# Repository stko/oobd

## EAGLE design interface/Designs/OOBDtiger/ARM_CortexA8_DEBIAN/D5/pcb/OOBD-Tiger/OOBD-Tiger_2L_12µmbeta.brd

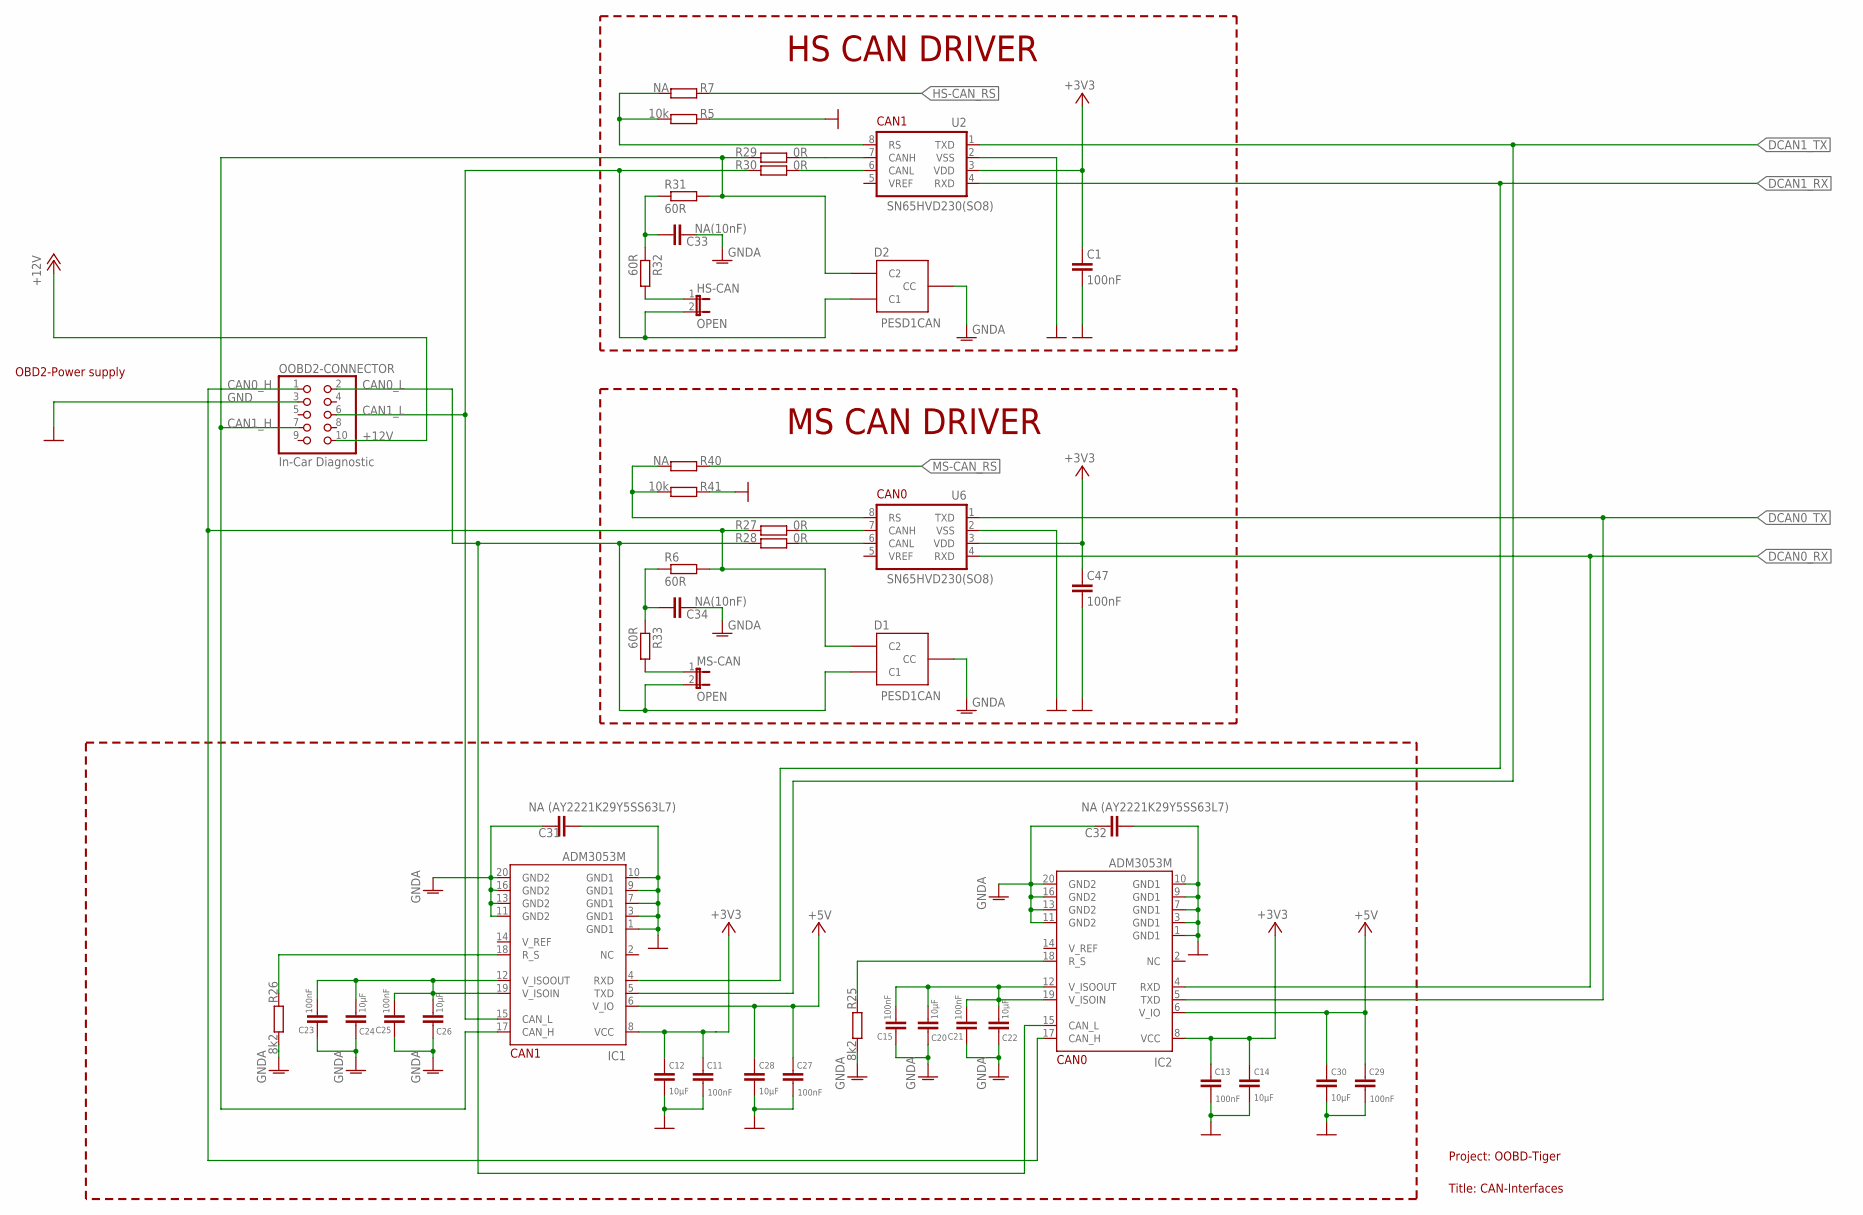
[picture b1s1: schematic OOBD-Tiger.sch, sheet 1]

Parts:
C1, C11, C13, C15, C21, C23, C25, C27, C29, C47: 100nF; C0603K
C12, C14, C20, C22, C24, C26, C28, C30: 10µF; C0805K
C31, C32: NA (AY2221K29Y5SS63L7); C075-032X103
C33, C34: NA(10nF); C0603
D1, D2: PESD1CAN; SOT23
HS-CAN: OPEN; 1X02
IC1, IC2: ADM3053M; SO20W
MS-CAN: OPEN; 1X02
OOBD2-CONNECTOR: In-Car Diagnostic; 2X05/90
R5, R41: 10k; R0603
R6, R31, R32, R33: 60R; R0603
R7, R40: NA; R0603
R25, R26: 8k2; R0603
R27, R28, R29, R30: 0R; 0207/10
U2, U6: SN65HVD230(SO8); SO-08

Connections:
+3V3: C1.1, C11.1, C12.1, C13.1, C14.1, C47.1, IC1.8 (VCC), IC2.8 (VCC), U2.3 (VDD), U6.3 (VDD); also elsewhere on the board
+5V: C27.1, C28.1, C29.1, C30.1, IC1.6 (V_IO), IC2.6 (V_IO); also elsewhere on the board
+12V: OOBD2-CONNECTOR.10; also elsewhere on the board
CAN0_H: D1.2 (C2), IC2.17 (CAN_H), OOBD2-CONNECTOR.1, R6.2, R27.1
CAN0_L: D1.1 (C1), IC2.15 (CAN_L), MS-CAN.2, OOBD2-CONNECTOR.2, R28.1
CAN1_H: D2.2 (C2), IC1.17 (CAN_H), OOBD2-CONNECTOR.7, R29.2, R31.2
CAN1_L: D2.1 (C1), HS-CAN.2, IC1.15 (CAN_L), OOBD2-CONNECTOR.6, R30.1
DCAN0_RX: IC2.4 (RXD), U6.4 (RXD); also elsewhere on the board
DCAN0_TX: IC2.5 (TXD), U6.1 (TXD); also elsewhere on the board
DCAN1_RX: IC1.4 (RXD), U2.4 (RXD); also elsewhere on the board
DCAN1_TX: IC1.5 (TXD), U2.1 (TXD); also elsewhere on the board
GND: C1.2, C11.2, C12.2, C13.2, C14.2, C27.2, C28.2, C29.2, C30.2, C31.2, C32.2, C47.2, IC1.1 (GND1), IC1.3 (GND1), IC1.7 (GND1), IC1.9 (GND1), IC1.10 (GND1), IC2.1 (GND1), IC2.3 (GND1), IC2.7 (GND1), IC2.9 (GND1), IC2.10 (GND1), OOBD2-CONNECTOR.3, R5.2, R41.2, U2.2 (VSS), U6.2 (VSS); also elsewhere on the board
GNDA: C15.2, C20.2, C21.2, C22.2, C23.2, C24.2, C25.2, C26.2, C31.1, C32.1, C33.2, C34.2, D1.3 (CC), D2.3 (CC), IC1.11 (GND2), IC1.13 (GND2), IC1.16 (GND2), IC1.20 (GND2), IC2.11 (GND2), IC2.13 (GND2), IC2.16 (GND2), IC2.20 (GND2), R25.1, R26.1
HS-CAN_RS: R7.2; also elsewhere on the board
MS-CAN_RS: R40.2; also elsewhere on the board
unnamed: C33.1, R31.1, R32.1
unnamed: R5.1, R7.1, U2.8 (RS)
unnamed: C34.1, R6.1, R33.1
unnamed: HS-CAN.1, R32.2
unnamed: C23.1, C24.1, C25.1, C26.1, IC1.12 (V_ISOOUT), IC1.19 (V_ISOIN)
unnamed: MS-CAN.1, R33.2
unnamed: IC2.18 (R_S), R25.2
unnamed: R27.2, U6.7 (CANH)
unnamed: R30.2, U2.6 (CANL)
unnamed: R28.2, U6.6 (CANL)
unnamed: R29.1, U2.7 (CANH)
unnamed: C15.1, C20.1, C21.1, C22.1, IC2.12 (V_ISOOUT), IC2.19 (V_ISOIN)
unnamed: IC1.18 (R_S), R26.2
unnamed: R40.1, R41.1, U6.8 (RS)

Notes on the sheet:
MS CAN DRIVER
HS CAN DRIVER
Project: OOBD-Tiger
Title: CAN-Interfaces
OBD2-Power supply
CAN1
CAN0

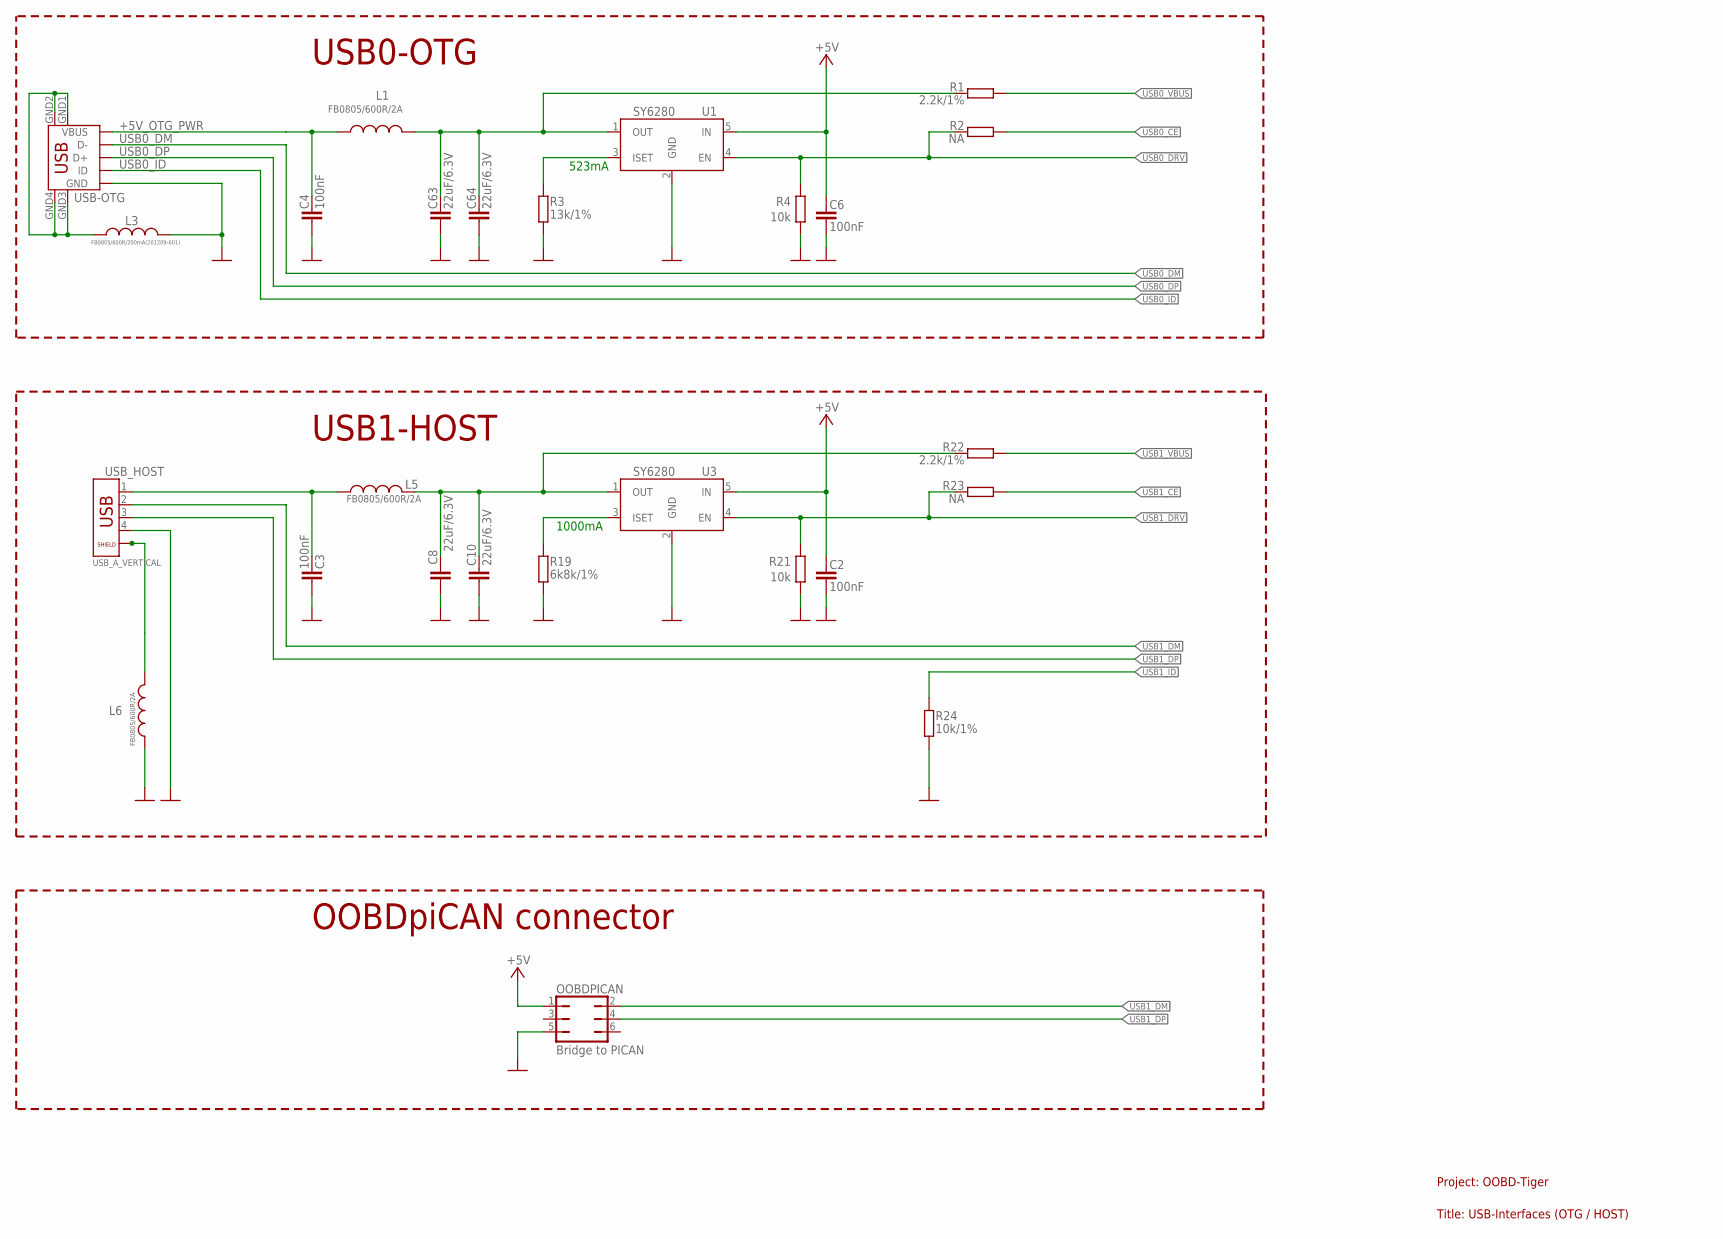
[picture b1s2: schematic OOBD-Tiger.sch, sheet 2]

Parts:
C2, C3, C4, C6: 100nF; C0603K
C8, C10, C63, C64: 22uF/6.3V; C0603
L1, L5, L6: FB0805/600R/2A; L0603
L3: FB0805/600R/200mA(201209-601); L0603
OOBDPICAN: Bridge to PICAN; JP3Q
R1, R22: 2.2k/1%; R0603
R2, R23: NA; R0603
R3: 13k/1%; R0603
R4, R21: 10k; R0603
R19: 6k8k/1%; R0603
R24: 10k/1%; R0603
U1, U3: SY6280; SOT23-5
USB_HOST: USB_A_VERTICAL; USB_PN87520_DEV_PTH
USB_OTG: USB-OTG; USB_MINI_9PIN

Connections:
+5V: C2.1, C6.1, OOBDPICAN.1, U1.5 (IN), U3.5 (IN); also elsewhere on the board
+5V_OTG_PWR: C4.1, L1.1, USB_OTG.VBUS
GND: C2.2, C3.2, C4.2, C6.2, C8.2, C10.2, C63.2, C64.2, L3.1, L6.1, OOBDPICAN.5, R3.1, R4.1, R19.1, R21.1, R24.1, U1.2 (GND), U3.2 (GND), USB_HOST.4, USB_OTG.GND; also elsewhere on the board
unnamed: R19.2, U3.3 (ISET)
unnamed: C8.1, C10.1, L5.1, R22.2, U3.1 (OUT)
unnamed: C3.1, L5.2, USB_HOST.1
unnamed: L6.2, USB_HOST.P$1 (5), USB_HOST.P$2 (6)
unnamed: R3.2, U1.3 (ISET)
unnamed: C63.1, C64.1, L1.2, R1.2, U1.1 (OUT)
unnamed: L3.2, USB_OTG.GND1, USB_OTG.GND2, USB_OTG.GND3, USB_OTG.GND4
USB0_CE: R2.2; also elsewhere on the board
USB0_DM: USB_OTG.D-; also elsewhere on the board
USB0_DP: USB_OTG.D+; also elsewhere on the board
USB0_DRV: R2.1, R4.2, U1.4 (EN); also elsewhere on the board
USB0_ID: USB_OTG.ID; also elsewhere on the board
USB0_VBUS: R1.1; also elsewhere on the board
USB1_CE: R23.2; also elsewhere on the board
USB1_DM: OOBDPICAN.2, USB_HOST.2; also elsewhere on the board
USB1_DP: OOBDPICAN.4, USB_HOST.3; also elsewhere on the board
USB1_DRV: R21.2, R23.1, U3.4 (EN); also elsewhere on the board
USB1_ID: R24.2; also elsewhere on the board
USB1_VBUS: R22.1; also elsewhere on the board

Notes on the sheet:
USB0-OTG
Project: OOBD-Tiger
Title: USB-Interfaces (OTG / HOST)
USB1-HOST
523mA
1000mA
OOBDpiCAN connector

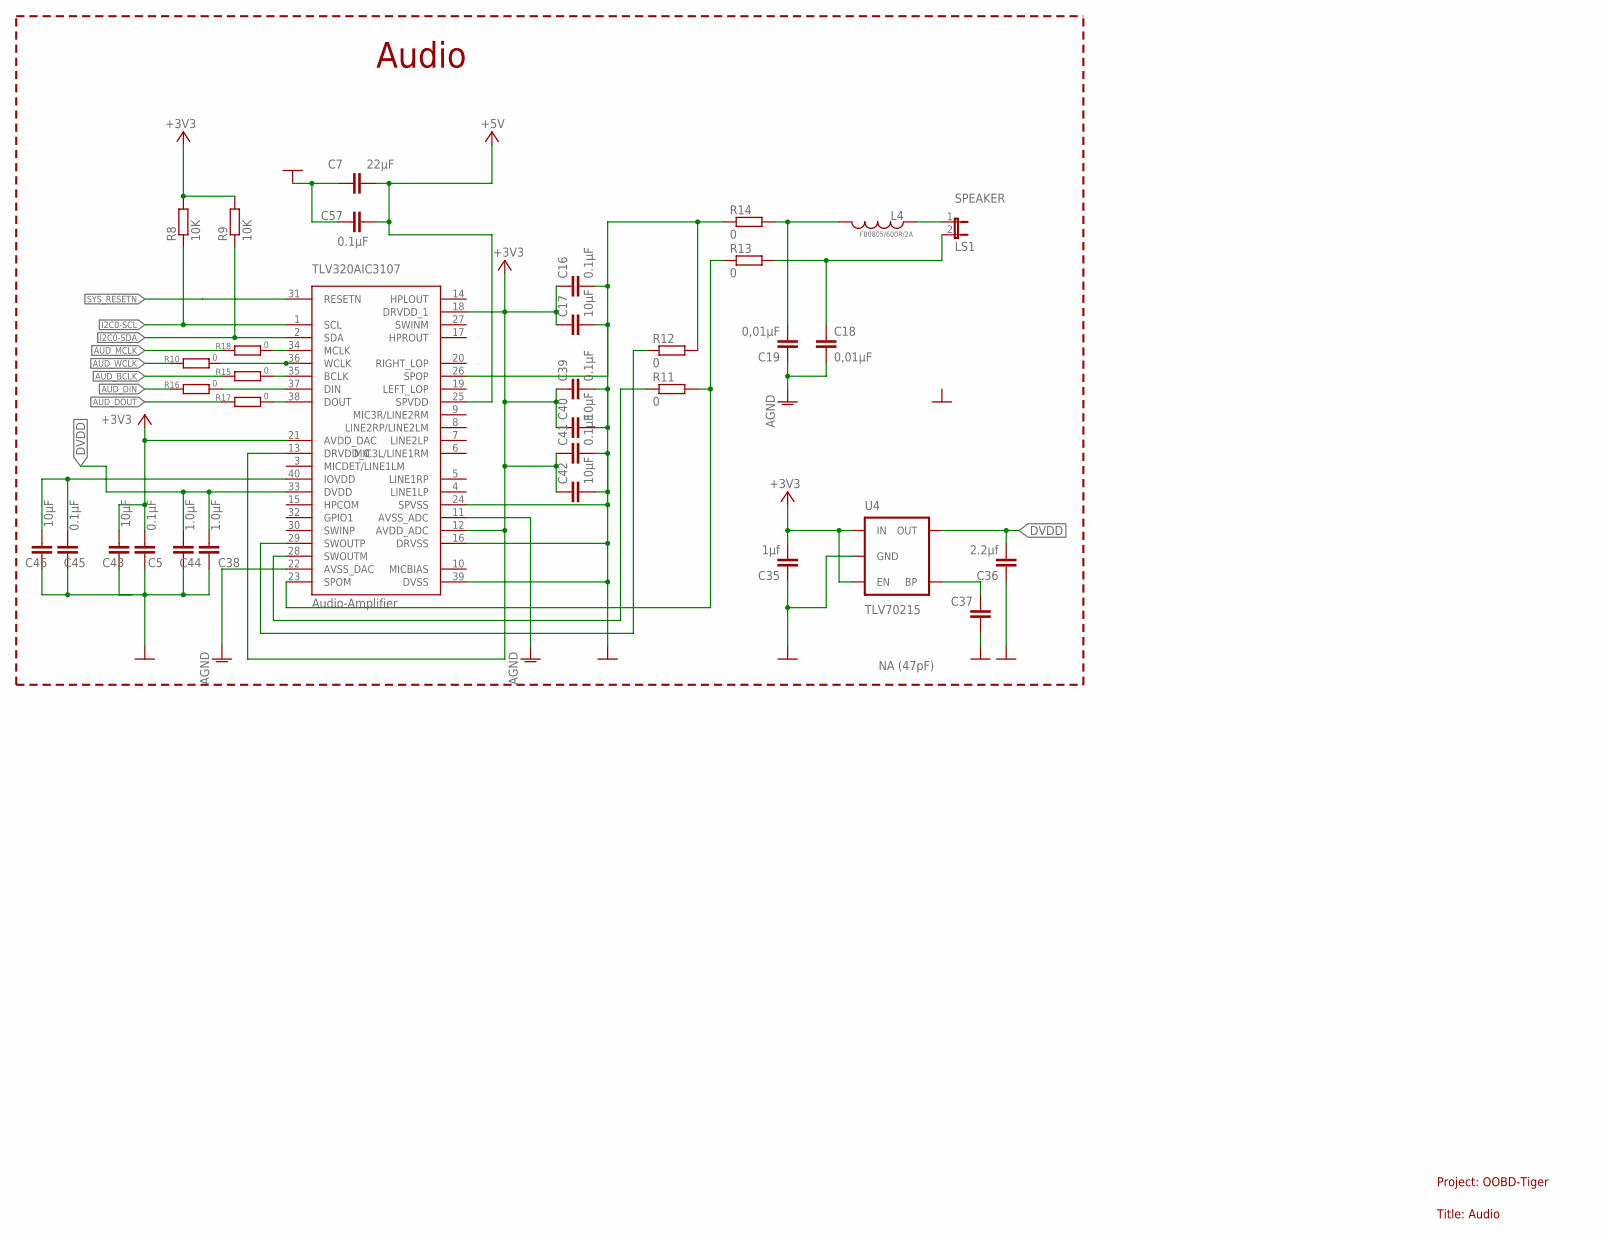
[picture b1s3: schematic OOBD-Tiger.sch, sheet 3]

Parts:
C5, C16, C39, C41, C45, C57: 0.1µF; 0603-CAP
C7: 22µF; 0603-CAP
C17, C40, C42, C43, C46: 10µF; 0603-CAP
C18, C19: 0,01µF; 0603-CAP
C35: 1µf; 0603-CAP
C36: 2.2µf; 0603-CAP
C37: NA (47pF); 0603-CAP
C38, C44: 1.0µF; 0603-CAP
L4: FB0805/600R/2A; L0603
R8, R9: 10K; R0603
R10, R11, R12, R13, R14, R15, R16, R17, R18: 0; R0603
SPEAKER: LS1; 1X02
TLV320AIC3107: Audio-Amplifier; QFN40-6X6
U4: TLV70215; SOT23-5

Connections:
+3V3: C5.2, C16.1, C17.1, C35.2, C39.1, C40.1, C41.1, C42.1, C43.2, R8.2, R9.2, TLV320AIC3107.12 (AVDD_ADC), TLV320AIC3107.13 (DRVDD_0), TLV320AIC3107.18 (DRVDD_1), TLV320AIC3107.21 (AVDD_DAC), U4.1 (IN), U4.3 (EN); also elsewhere on the board
+5V: C7.2, C57.2, TLV320AIC3107.25 (SPVDD); also elsewhere on the board
AGND: C18.2, C19.1, TLV320AIC3107.11 (AVSS_ADC), TLV320AIC3107.22 (AVSS_DAC)
AUD_BCLK: R15.1; also elsewhere on the board
AUD_DIN: R16.1; also elsewhere on the board
AUD_DOUT: R17.1; also elsewhere on the board
AUD_MCLK: R18.1; also elsewhere on the board
AUD_WCLK: R10.1; also elsewhere on the board
DVDD: C36.2, C38.2, C44.2, TLV320AIC3107.33 (DVDD), U4.5 (OUT)
GND: C5.1, C7.1, C16.2, C17.2, C35.1, C36.1, C37.1, C38.1, C39.2, C40.2, C41.2, C42.2, C43.1, C44.1, C57.1, R12.2, R14.1, TLV320AIC3107.16 (DRVSS), TLV320AIC3107.24 (SPVSS), TLV320AIC3107.26 (SPOP), TLV320AIC3107.39 (DVSS), U4.2 (GND); also elsewhere on the board
GND1: C45.1, C46.1
I2C0-SCL: R8.1, TLV320AIC3107.1 (SCL); also elsewhere on the board
I2C0-SDA: R9.1, TLV320AIC3107.2 (SDA); also elsewhere on the board
unnamed: C37.2, U4.4 (BP)
unnamed: C19.2, L4.2, R14.2
unnamed: C18.1, R13.2, SPEAKER.2
unnamed: L4.1, SPEAKER.1
unnamed: R11.2, R13.1, TLV320AIC3107.23 (SPOM)
unnamed: R11.1, TLV320AIC3107.28 (SWOUTM)
unnamed: R12.1, TLV320AIC3107.29 (SWOUTP)
unnamed: C45.2, C46.2, TLV320AIC3107.40 (IOVDD)
unnamed: R17.2, TLV320AIC3107.38 (DOUT)
unnamed: R16.2, TLV320AIC3107.37 (DIN)
unnamed: R15.2, TLV320AIC3107.35 (BCLK)
unnamed: R10.2, TLV320AIC3107.36 (WCLK)
unnamed: R18.2, TLV320AIC3107.34 (MCLK)
SYS_RESETN: TLV320AIC3107.31 (RESETN); also elsewhere on the board

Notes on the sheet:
Project: OOBD-Tiger
Title: Audio
Audio

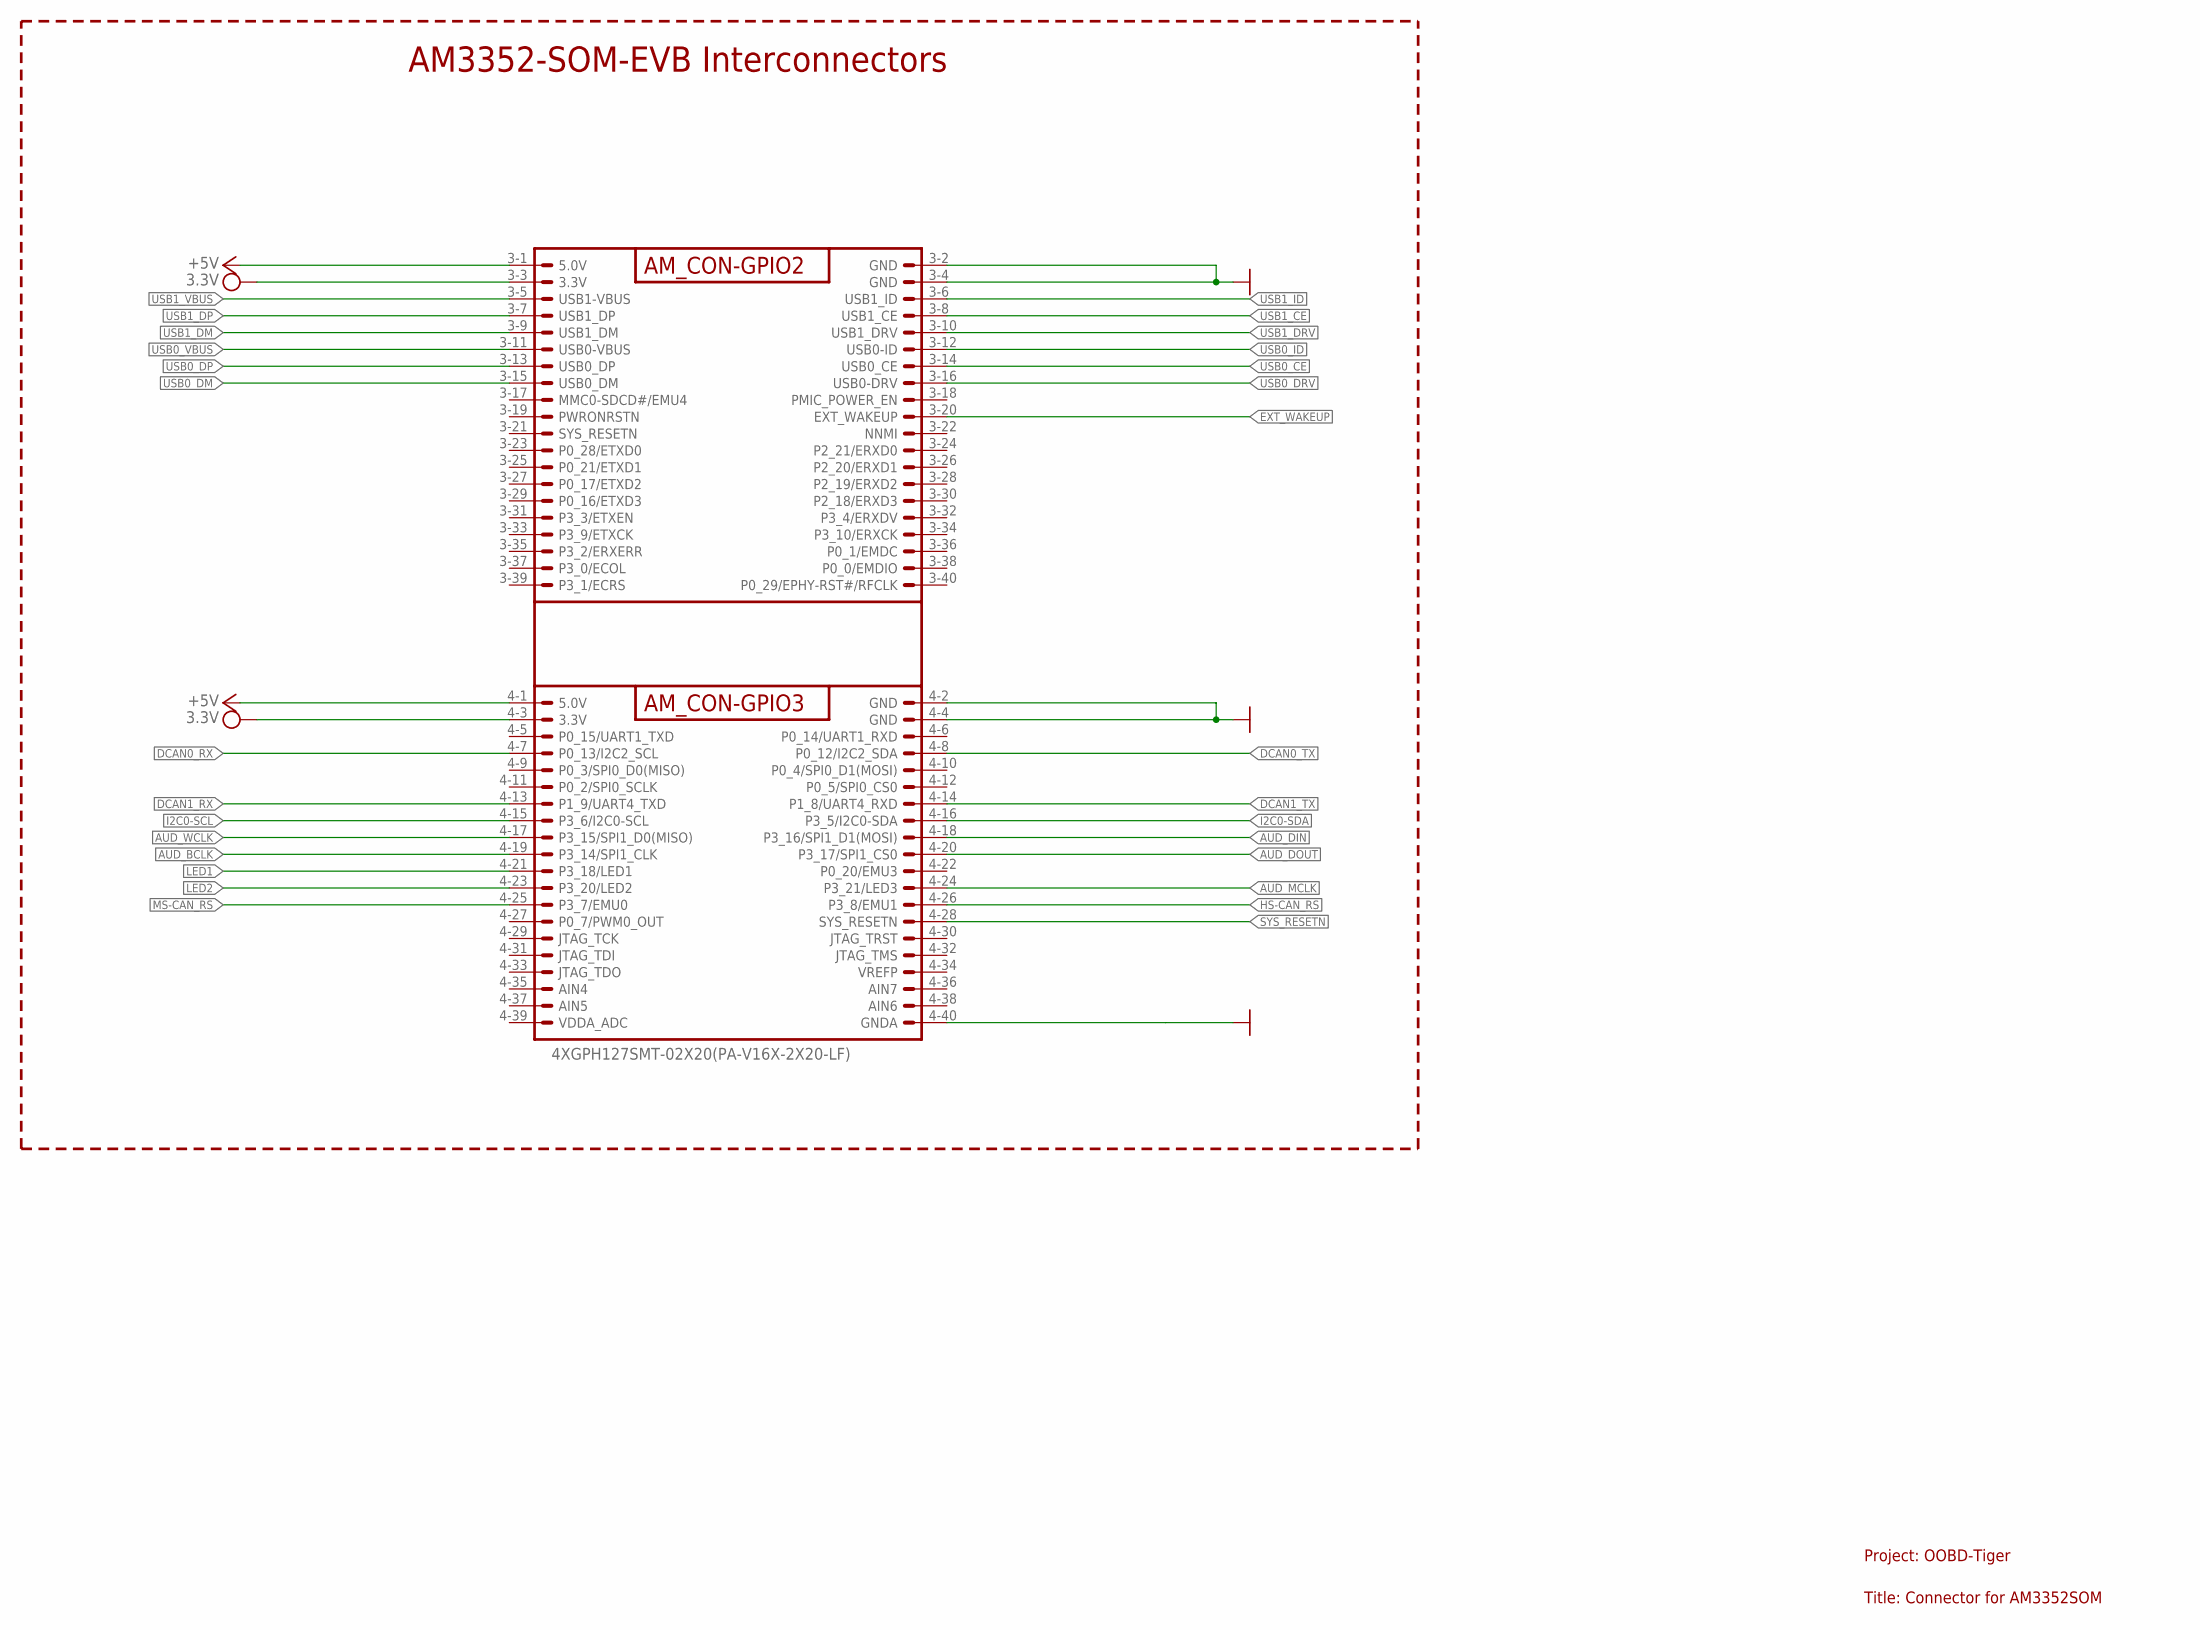
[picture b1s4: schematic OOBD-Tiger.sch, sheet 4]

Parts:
AM3352-SOM-EVB-PLATFORM: 4XGPH127SMT-02X20(PA-V16X-2X20-LF); OOBD-TIGER-AM3352-SOM

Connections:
3V3: AM3352-SOM-EVB-PLATFORM.3-3 (3.3V), AM3352-SOM-EVB-PLATFORM.4-3 (3.3V)
+5V: AM3352-SOM-EVB-PLATFORM.3-1 (5.0V), AM3352-SOM-EVB-PLATFORM.4-1 (5.0V); also elsewhere on the board
AUD_BCLK: AM3352-SOM-EVB-PLATFORM.4-19 (P3_14/SPI1_CLK); also elsewhere on the board
AUD_DIN: AM3352-SOM-EVB-PLATFORM.4-18 (P3_16/SPI1_D1(MOSI)); also elsewhere on the board
AUD_DOUT: AM3352-SOM-EVB-PLATFORM.4-20 (P3_17/SPI1_CS0); also elsewhere on the board
AUD_MCLK: AM3352-SOM-EVB-PLATFORM.4-24 (P3_21/LED3); also elsewhere on the board
AUD_WCLK: AM3352-SOM-EVB-PLATFORM.4-17 (P3_15/SPI1_D0(MISO)); also elsewhere on the board
DCAN0_RX: AM3352-SOM-EVB-PLATFORM.4-7 (P0_13/I2C2_SCL); also elsewhere on the board
DCAN0_TX: AM3352-SOM-EVB-PLATFORM.4-8 (P0_12/I2C2_SDA); also elsewhere on the board
DCAN1_RX: AM3352-SOM-EVB-PLATFORM.4-13 (P1_9/UART4_TXD); also elsewhere on the board
DCAN1_TX: AM3352-SOM-EVB-PLATFORM.4-14 (P1_8/UART4_RXD); also elsewhere on the board
EXT_WAKEUP: AM3352-SOM-EVB-PLATFORM.3-20 (EXT_WAKEUP); also elsewhere on the board
GND: AM3352-SOM-EVB-PLATFORM.3-2 (GND), AM3352-SOM-EVB-PLATFORM.3-4 (GND), AM3352-SOM-EVB-PLATFORM.4-2 (GND), AM3352-SOM-EVB-PLATFORM.4-4 (GND), AM3352-SOM-EVB-PLATFORM.4-40 (GNDA); also elsewhere on the board
HS-CAN_RS: AM3352-SOM-EVB-PLATFORM.4-26 (P3_8/EMU1); also elsewhere on the board
I2C0-SCL: AM3352-SOM-EVB-PLATFORM.4-15 (P3_6/I2C0-SCL); also elsewhere on the board
I2C0-SDA: AM3352-SOM-EVB-PLATFORM.4-16 (P3_5/I2C0-SDA); also elsewhere on the board
LED1: AM3352-SOM-EVB-PLATFORM.4-21 (P3_18/LED1); also elsewhere on the board
LED2: AM3352-SOM-EVB-PLATFORM.4-23 (P3_20/LED2); also elsewhere on the board
MS-CAN_RS: AM3352-SOM-EVB-PLATFORM.4-25 (P3_7/EMU0); also elsewhere on the board
SYS_RESETN: AM3352-SOM-EVB-PLATFORM.4-28 (SYS_RESETN); also elsewhere on the board
USB0_CE: AM3352-SOM-EVB-PLATFORM.3-14 (USB0_CE); also elsewhere on the board
USB0_DM: AM3352-SOM-EVB-PLATFORM.3-15 (USB0_DM); also elsewhere on the board
USB0_DP: AM3352-SOM-EVB-PLATFORM.3-13 (USB0_DP); also elsewhere on the board
USB0_DRV: AM3352-SOM-EVB-PLATFORM.3-16 (USB0-DRV); also elsewhere on the board
USB0_ID: AM3352-SOM-EVB-PLATFORM.3-12 (USB0-ID); also elsewhere on the board
USB0_VBUS: AM3352-SOM-EVB-PLATFORM.3-11 (USB0-VBUS); also elsewhere on the board
USB1_CE: AM3352-SOM-EVB-PLATFORM.3-8 (USB1_CE); also elsewhere on the board
USB1_DM: AM3352-SOM-EVB-PLATFORM.3-9 (USB1_DM); also elsewhere on the board
USB1_DP: AM3352-SOM-EVB-PLATFORM.3-7 (USB1_DP); also elsewhere on the board
USB1_DRV: AM3352-SOM-EVB-PLATFORM.3-10 (USB1_DRV); also elsewhere on the board
USB1_ID: AM3352-SOM-EVB-PLATFORM.3-6 (USB1_ID); also elsewhere on the board
USB1_VBUS: AM3352-SOM-EVB-PLATFORM.3-5 (USB1-VBUS); also elsewhere on the board

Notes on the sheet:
AM3352-SOM-EVB Interconnectors
Project: OOBD-Tiger
Title: Connector for AM3352SOM

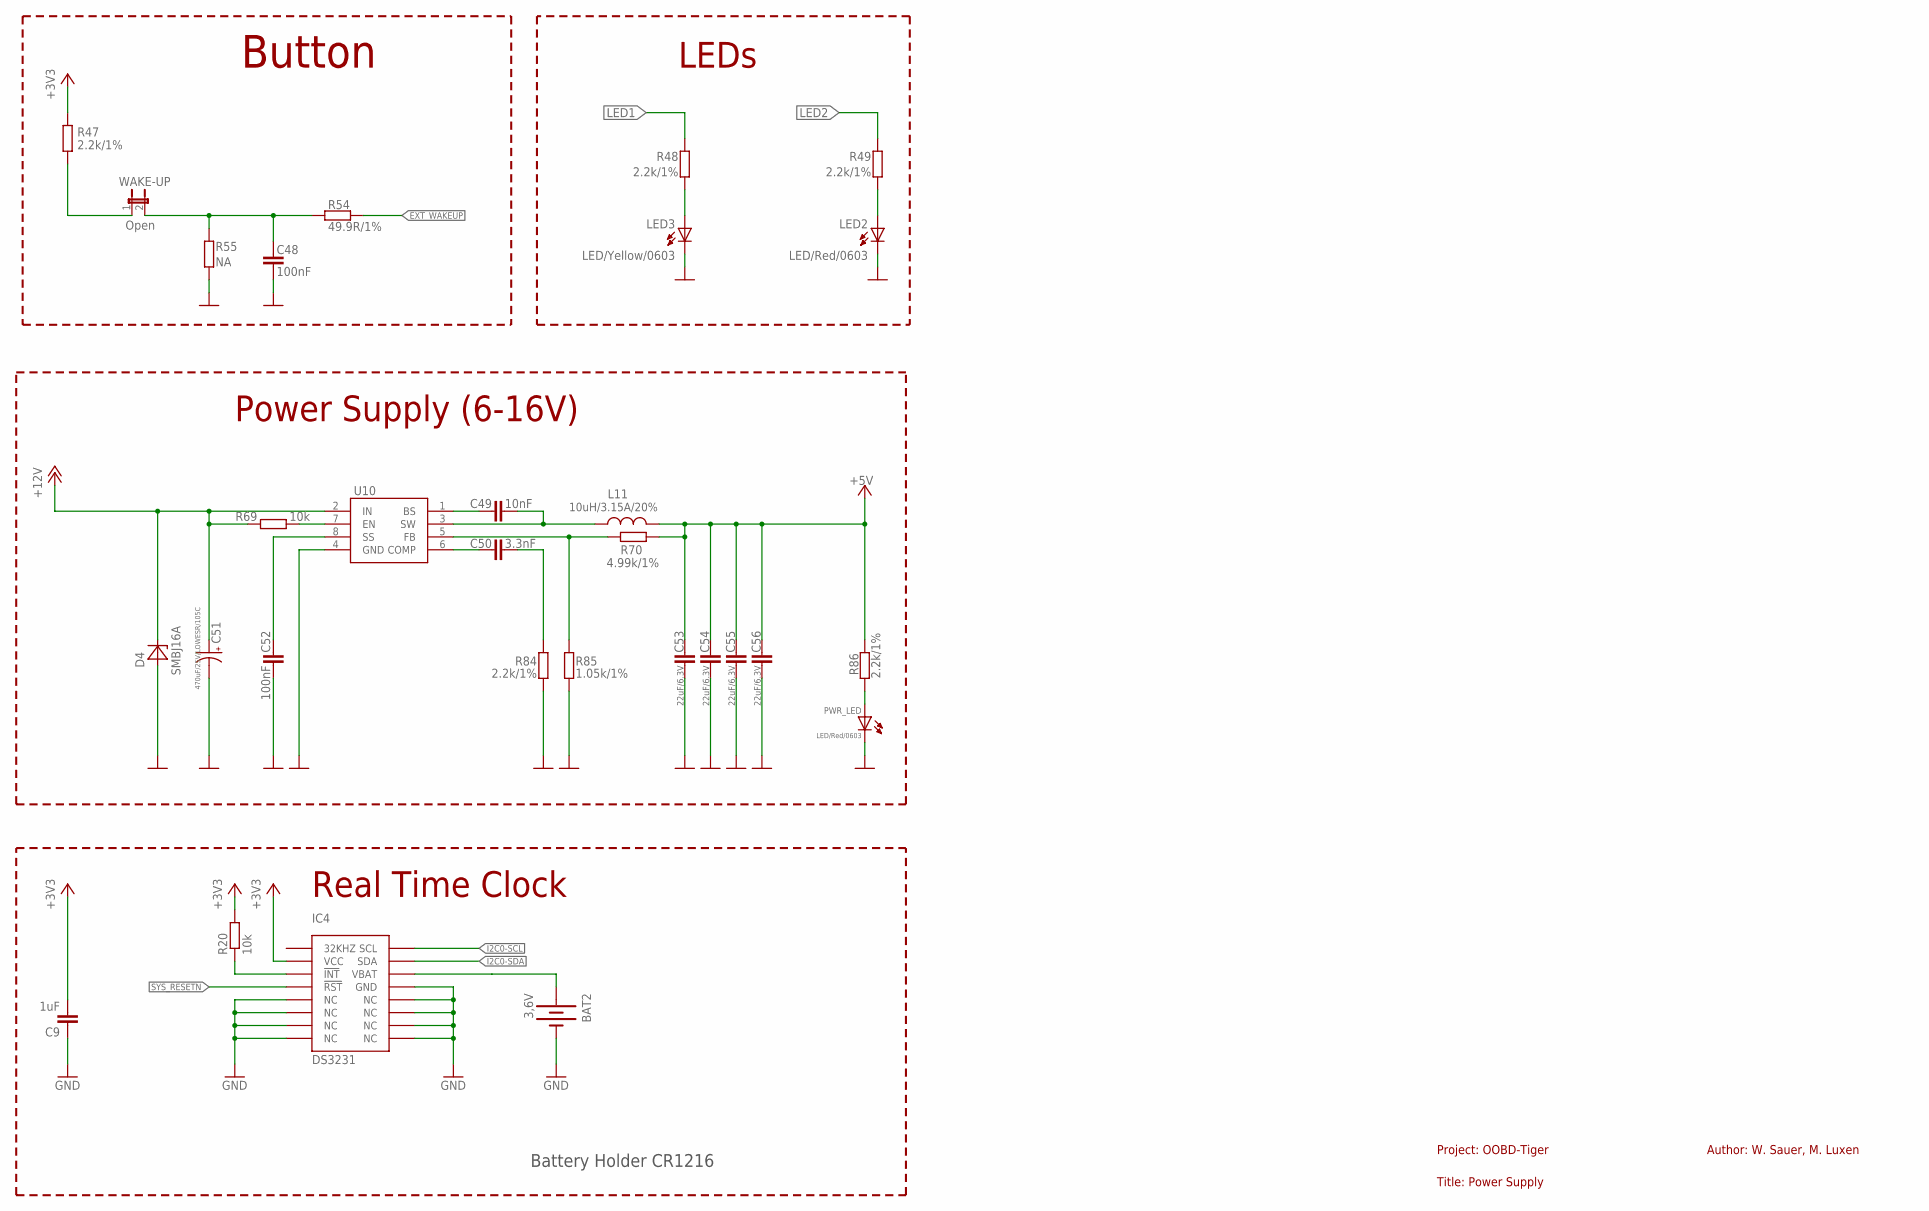
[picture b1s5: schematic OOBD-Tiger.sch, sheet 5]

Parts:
BAT2: 3,6V; BATTCON_12MM_PTH
C9: 1uF; C0603
C48, C52: 100nF; C0603
C49: 10nF; C0603
C50: 3.3nF; C0603
C51: 470uF/25V/LOWESR/105C; PANASONIC_D
C53, C54, C55, C56: 22uF/6.3V; C0603
D4: SMBJ16A; DO214AA
IC4: DS3231; SOIC-16W
L11: 10uH/3.15A/20%; 8X8MM_3131
LED2: LED/Red/0603; LED_0603
LED3: LED/Yellow/0603; LED_0603
PWR_LED: LED/Red/0603; LED-0603
R20, R69: 10k; R0603
R47, R48, R49, R84, R86: 2.2k/1%; R0603
R54: 49.9R/1%; R0603
R55: NA; R0603
R70: 4.99k/1%; R0603
R85: 1.05k/1%; R0603
U10: MP1482DS; SOIC8
WAKE-UP: Open; 1X02_LOCK

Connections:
+3V3: C9.2, IC4.2 (VCC), R20.2, R47.2; also elsewhere on the board
+5V: C53.1, C54.1, C55.1, C56.1, L11.2, R70.2, R86.1; also elsewhere on the board
+12V: C51.+, D4.C, R69.1, U10.2 (IN); also elsewhere on the board
EXT_WAKEUP: R54.1; also elsewhere on the board
GND: BAT2.GND (-), C9.1, C48.2, C51.-, C52.2, C53.2, C54.2, C55.2, C56.2, D4.A, IC4.5 (NC), IC4.6 (NC), IC4.7 (NC), IC4.8 (NC), IC4.9 (NC), IC4.10 (NC), IC4.11 (NC), IC4.12 (NC), IC4.13 (GND), LED2.C, LED3.C, PWR_LED.C, R55.2, R84.2, R85.2, U10.4 (GND); also elsewhere on the board
I2C0-SCL: IC4.16 (SCL); also elsewhere on the board
I2C0-SDA: IC4.15 (SDA); also elsewhere on the board
LED1: R48.1; also elsewhere on the board
LED2: R49.1; also elsewhere on the board
unnamed: LED2.A, R49.2
unnamed: C52.1, U10.8 (SS)
unnamed: R69.2, U10.7 (EN)
unnamed: C49.1, U10.1 (BS)
unnamed: C49.2, L11.1, U10.3 (SW)
unnamed: C50.1, U10.6 (COMP)
unnamed: C50.2, R84.1
unnamed: IC4.3 (!INT), R20.1
unnamed: R47.1, WAKE-UP.1
unnamed: C48.1, R54.2, R55.1, WAKE-UP.2
unnamed: R70.1, R85.1, U10.5 (FB)
unnamed: PWR_LED.A, R86.2
unnamed: LED3.A, R48.2
SYS_RESETN: IC4.4 (!RST); also elsewhere on the board
VBAT: BAT2.VCC@1 (+), IC4.14 (VBAT)

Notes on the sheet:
Button
LEDs
Power Supply (6-16V)
Author: W. Sauer, M. Luxen
Project: OOBD-Tiger
Title: Power Supply
Real Time Clock
Battery Holder CR1216

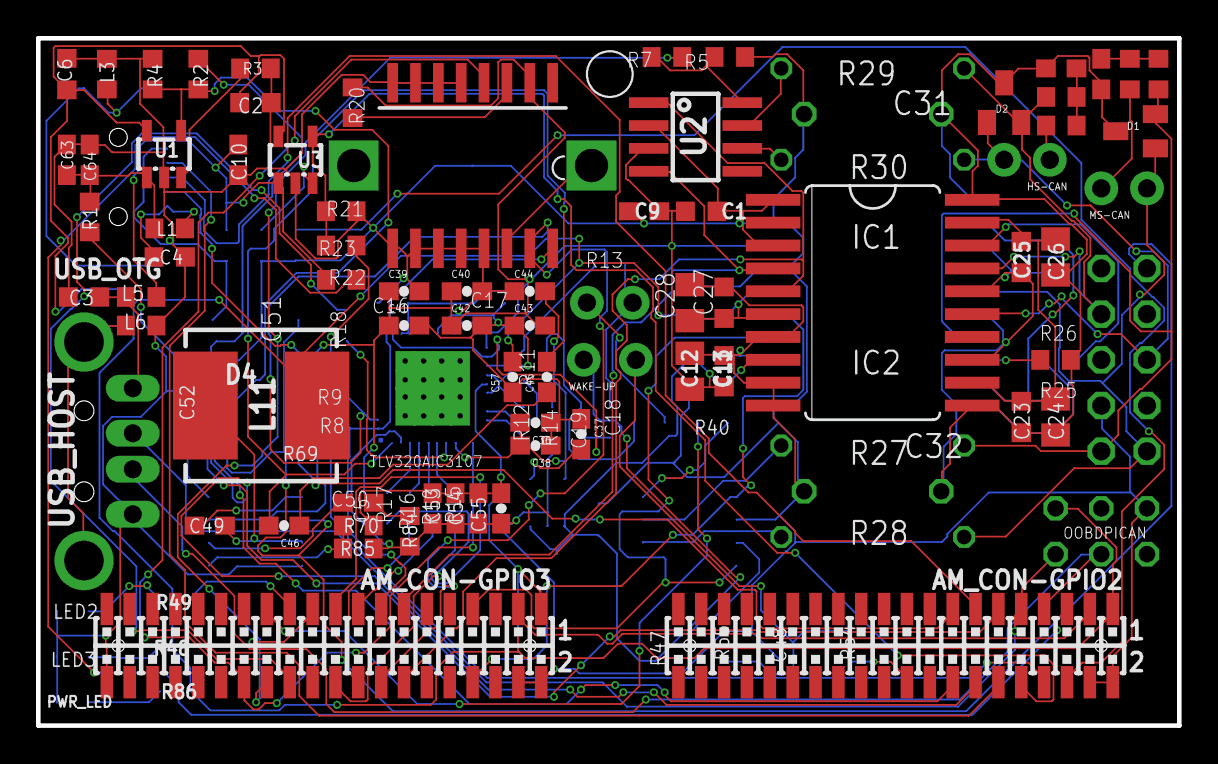
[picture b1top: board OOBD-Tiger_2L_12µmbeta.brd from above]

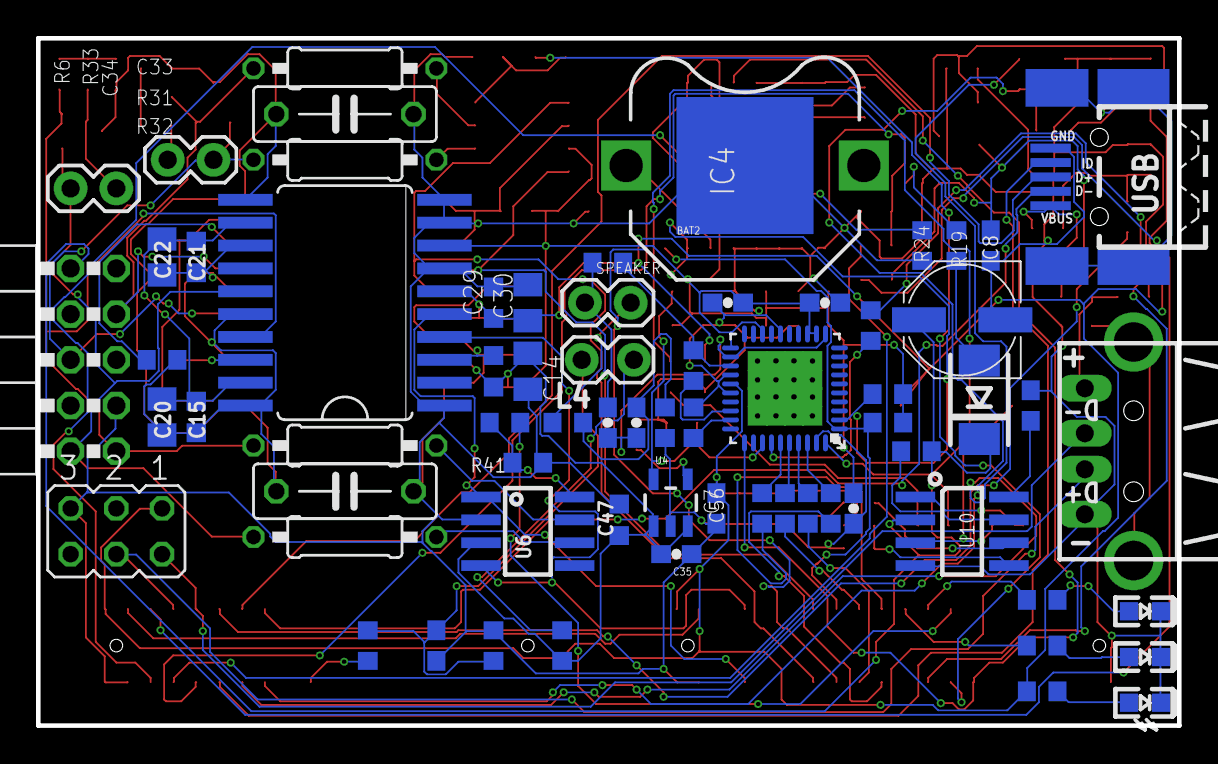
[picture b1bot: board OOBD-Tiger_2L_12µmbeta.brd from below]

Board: 2 copper layers, 63.4 x 38.2 mm, 136 parts (68 on the bottom side), 91 nets.

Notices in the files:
parts and their libraries:
SparkFun-Passives: Licensing: CC v3.0 Share-Alike You are welcome to use this library for commercial purposes.
SparkFun-Capacitors: Licensing: Creative Commons ShareAlike 4.0 International - https://creativecommons.org/licenses/by-sa/4.0
